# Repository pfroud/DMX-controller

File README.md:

# DMX controller

[DMX](https://en.wikipedia.org/wiki/DMX512) is an industry-standard protocol used for controlling stage lighting (and other things). This project is a rudimentary four-channel DMX controller. 

When working at an LED lighting company, I got some lamps from scrap and made some of them work enough to be useful. Those lamps are primarily controlled with DMX.

This project was my first time designing a PCB, and my first time doing 3D printing!!!

<table>
<tr>
<td></td>
<td></td>
<td></td>
</tr>
</table>

## Parts

* [Arduino Nano](https://en.wikipedia.org/wiki/Arduino_Nano) (not Micro, not Mini)
    * [DMXSerial library by Matthias Hertel](http://www.mathertel.de/Arduino/DMXSerial.aspx)
* Four slide potentiometers
* [TTL-to-RS485 transceiver from AliExpress](https://www.aliexpress.com/item/2251832519311238.html)
* A switch to disconnect the Arduino's RX & TX pins from the RS485 transceiver so the Arduino can be programmed over USB

The PCB was designed using [KiCad](https://www.kicad.org/) version 6 and fabricated by JLCPCB.

## Enclosure

<table>
<tr>
<td></td>
<td></td>
<td></td>
</tr>
</table>

I used Fusion 360 to design an enclosure to be 3D-printed.

The enclosure is not very good for multiple reasons. It was mostly a test to see if I can make something which fits the board and 3D-prints okay. Happily, my first attempt was successful.

The enclosure was printed on a Creality CR-6 SE using FilaCube PLA 2 filament.

## Prototype

In 2018, I made a prototype DMX controller without a PCB. It was pretty bad but it succeeded as a proof-of-concept.

<table>
<tr>
<td></td>
<td></td>
<td></td>
<td>
</tr>
</table>

The main parts used for the prototype were:

* [Arduino Uno](https://en.wikipedia.org/wiki/Arduino_Uno)
    * [DMXSerial library by Matthias Hertel](http://www.mathertel.de/Arduino/DMXSerial.aspx)
    * Prototype shield 
* [ST1480AC RS-485 transceiver](https://www.st.com/en/interfaces-and-transceivers/st1480ac.html)
* [3-gang electrical outlet box](https://www.homedepot.com/p/100404028)
* [Wago lever-nuts](https://www.wago.com/ca-en/lp-221)
* Three-pin [Molex KK 254](https://www.mattmillman.com/info/crimpconnectors/#kk100) connector

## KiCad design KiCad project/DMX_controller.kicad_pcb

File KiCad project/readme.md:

# KiCad project

Here's a screenshot of the schematic:

There's a DPDT switch is to disconnect the Arduino from the RS485 transceiver. The TX & RX pins must be disconnected form everything otherwise you can't upload sketches.<sup>[[1]](https://forum.arduino.cc/t/cant-upload-code-when-tx-rx-pins-are-connected/341202/4)[[2]](https://arduino.stackexchange.com/a/86)</sup>

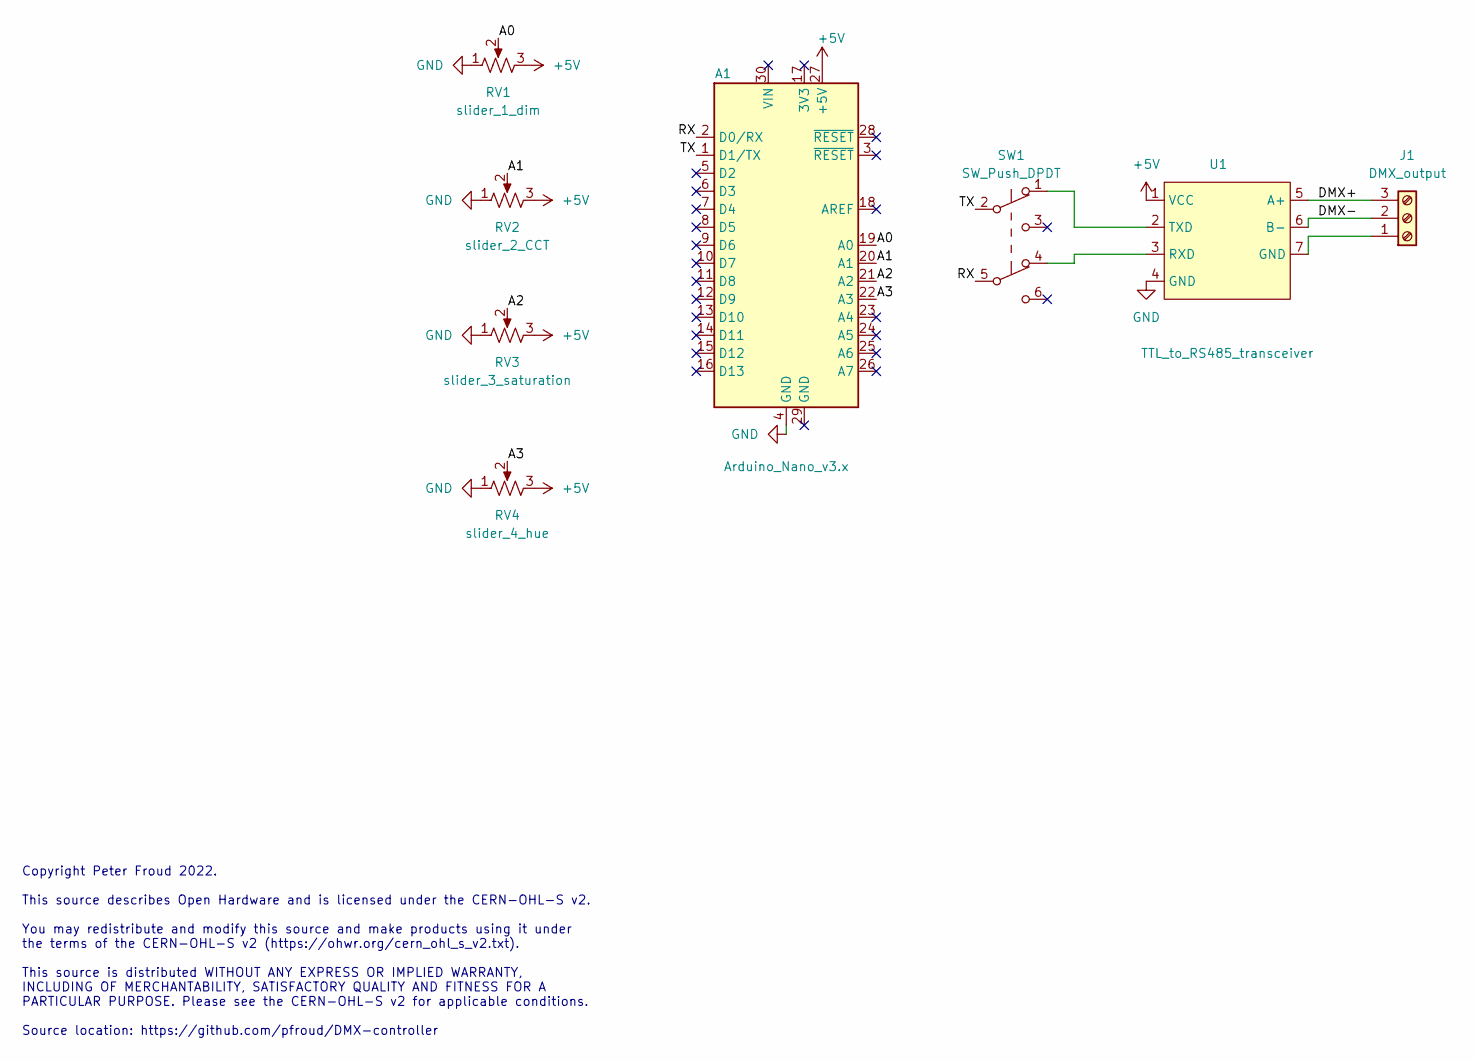
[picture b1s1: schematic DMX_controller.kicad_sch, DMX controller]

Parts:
A1: Arduino_Nano_v3.x; Arduino_Nano
J1: DMX_output; TerminalBlock_Phoenix_MKDS-3-3-5.08_1x03_P5.08mm_Horizontal
RV1: slider_1_dim; slide_potentiometer_OAK_A50K
RV2: slider_2_CCT; slide_potentiometer_OAK_A50K
RV3: slider_3_saturation; slide_potentiometer_OAK_A50K
RV4: slider_4_hue; slide_potentiometer_OAK_A50K
SW1: SW_Push_DPDT; slide_switch_DPDT_black_plastic_red_sealed_terminals
U1: TTL_to_RS485_transceiver

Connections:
+5V: A1.27 (+5V), RV1.3, RV2.3, RV3.3, RV4.3, U1.1 (VCC)
/A0: A1.19 (A0), RV1.2
/A1: A1.20 (A1), RV2.2
/A2: A1.21 (A2), RV3.2
/A3: A1.22 (A3), RV4.2
/DMX+: J1.3, U1.5 (A+)
/DMX-: J1.2, U1.6 (B-)
/RX: A1.2 (D0/RX), SW1.5 (B)
/TX: A1.1 (D1/TX), SW1.2 (B)
GND: A1.4 (GND), RV1.1, RV2.1, RV3.1, RV4.1, U1.4 (GND)
unnamed: J1.1, U1.7 (GND)
unnamed: SW1.1 (A), U1.2 (TXD)
unnamed: SW1.4 (A), U1.3 (RXD)

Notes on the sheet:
Copyright Peter Froud 2022. This source describes Open Hardware and is licensed under the CERN-OHL-S v2. You may redistribute and modify this source and make products using it under the terms of the CERN-OHL-S v2 (https://ohwr.org/cern_ohl_s_v2.txt). This source is distributed WITHOUT ANY EXPRESS O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

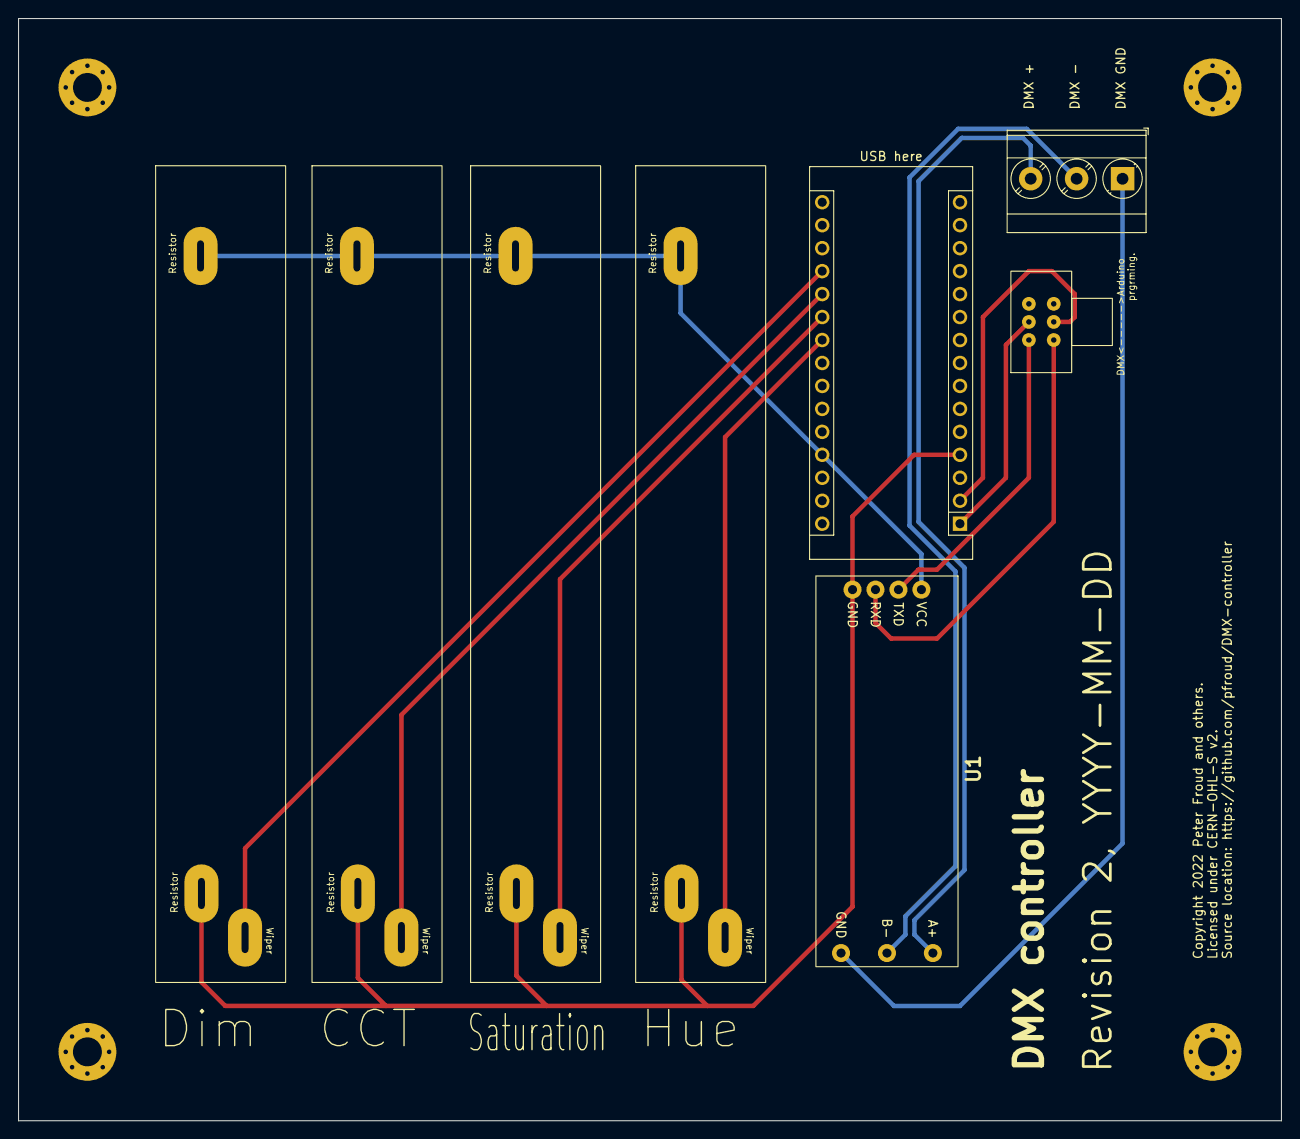
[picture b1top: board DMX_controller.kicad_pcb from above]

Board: 2 copper layers, 139.7 x 121.9 mm, 12 parts (0 on the bottom side), 13 nets.

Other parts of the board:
MH1, MH2, MH3, MH4: MountingHole_3.2mm_M3_Pad_Via

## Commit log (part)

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2022-06-27 Move KiCad project to subdirectory
2022-06-27 Add Arduino sketches
2022-06-28 Clean up 485 transceiver footprint+schematic
2022-06-28 Clean up schematic
2022-06-29 Make a real PCB!
2022-06-29 Correct slide potentiometer pin numbering
2022-06-29 Add reference material for slide potentiometer
2022-06-30 Increase track width from 0.25mm to 0.5mm
2022-06-30 Set date stamp for revision 1
2022-06-30 Add pads and vias to mounting holes
2022-07-03 Rotate screw terminal so 3D model is oriented
2022-07-03 Commit Gerber settings for JLCPCB
2022-07-03 Add 3D models to slide pot and screw terminal
2022-07-03 Add 3D model for Arduino Nano
2022-07-05 Set grid origin to use FreeCAD KiCadStepUp plugin
2022-07-05 Change Arduino Nano 3D model from x3d to step so FreeCAD can load it using KiCadStepUp plugin
    By Ahmed Abdelftah on GrabCAD
    https://grabcad.com/library/arduino-nano-case-3d-printed-1
2022-07-19 Add photos of rev 1 HW
2022-07-19 Add photos to readme
2022-07-20 Route DMX (RS-485) as differential pair
2022-07-20 Add CERN Open Hardware License Strongly Reciprocal
2022-07-20 Add KiCad screenshot
2022-07-20 Add note that I modified the Arduino Nano 3D model
2022-08-06 Add info about prototype
2022-08-06 Add documentation about Arduino sketches
2022-08-19 Move footprint pin 1 to 0,0
2022-08-22 Add info about 3D-printed enclosure
2022-09-06 Fix slide switch pads and fab
    The pitch is 2.00mm in the X direction and 2.75mm in the Y direction
2022-09-06 Fix silkscreen
2022-09-06 Fix courtyard
2022-09-06 Update PCB
2022-09-06 Ignore folder of gerbers
2022-09-06 Fix TTL-to-RS485 transceiver footprint pin spacing
2022-09-06 Update silkscreen and courtyard
2022-12-26 Clarify modifications to Arduino Nano 3D model
2023-03-26 Add readme for slide potentiometer
2023-03-26 Add readme for Kicad project

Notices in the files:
KiCad project/DMX_controller.kicad_pcb:
Copyright 2022 Peter Froud and others.
Licensed under CERN-OHL-S v2.
parts and their libraries:
Copyright Peter Froud 2022.: Eco1.User
